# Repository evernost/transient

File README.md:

# transient
An analog synthesizer.

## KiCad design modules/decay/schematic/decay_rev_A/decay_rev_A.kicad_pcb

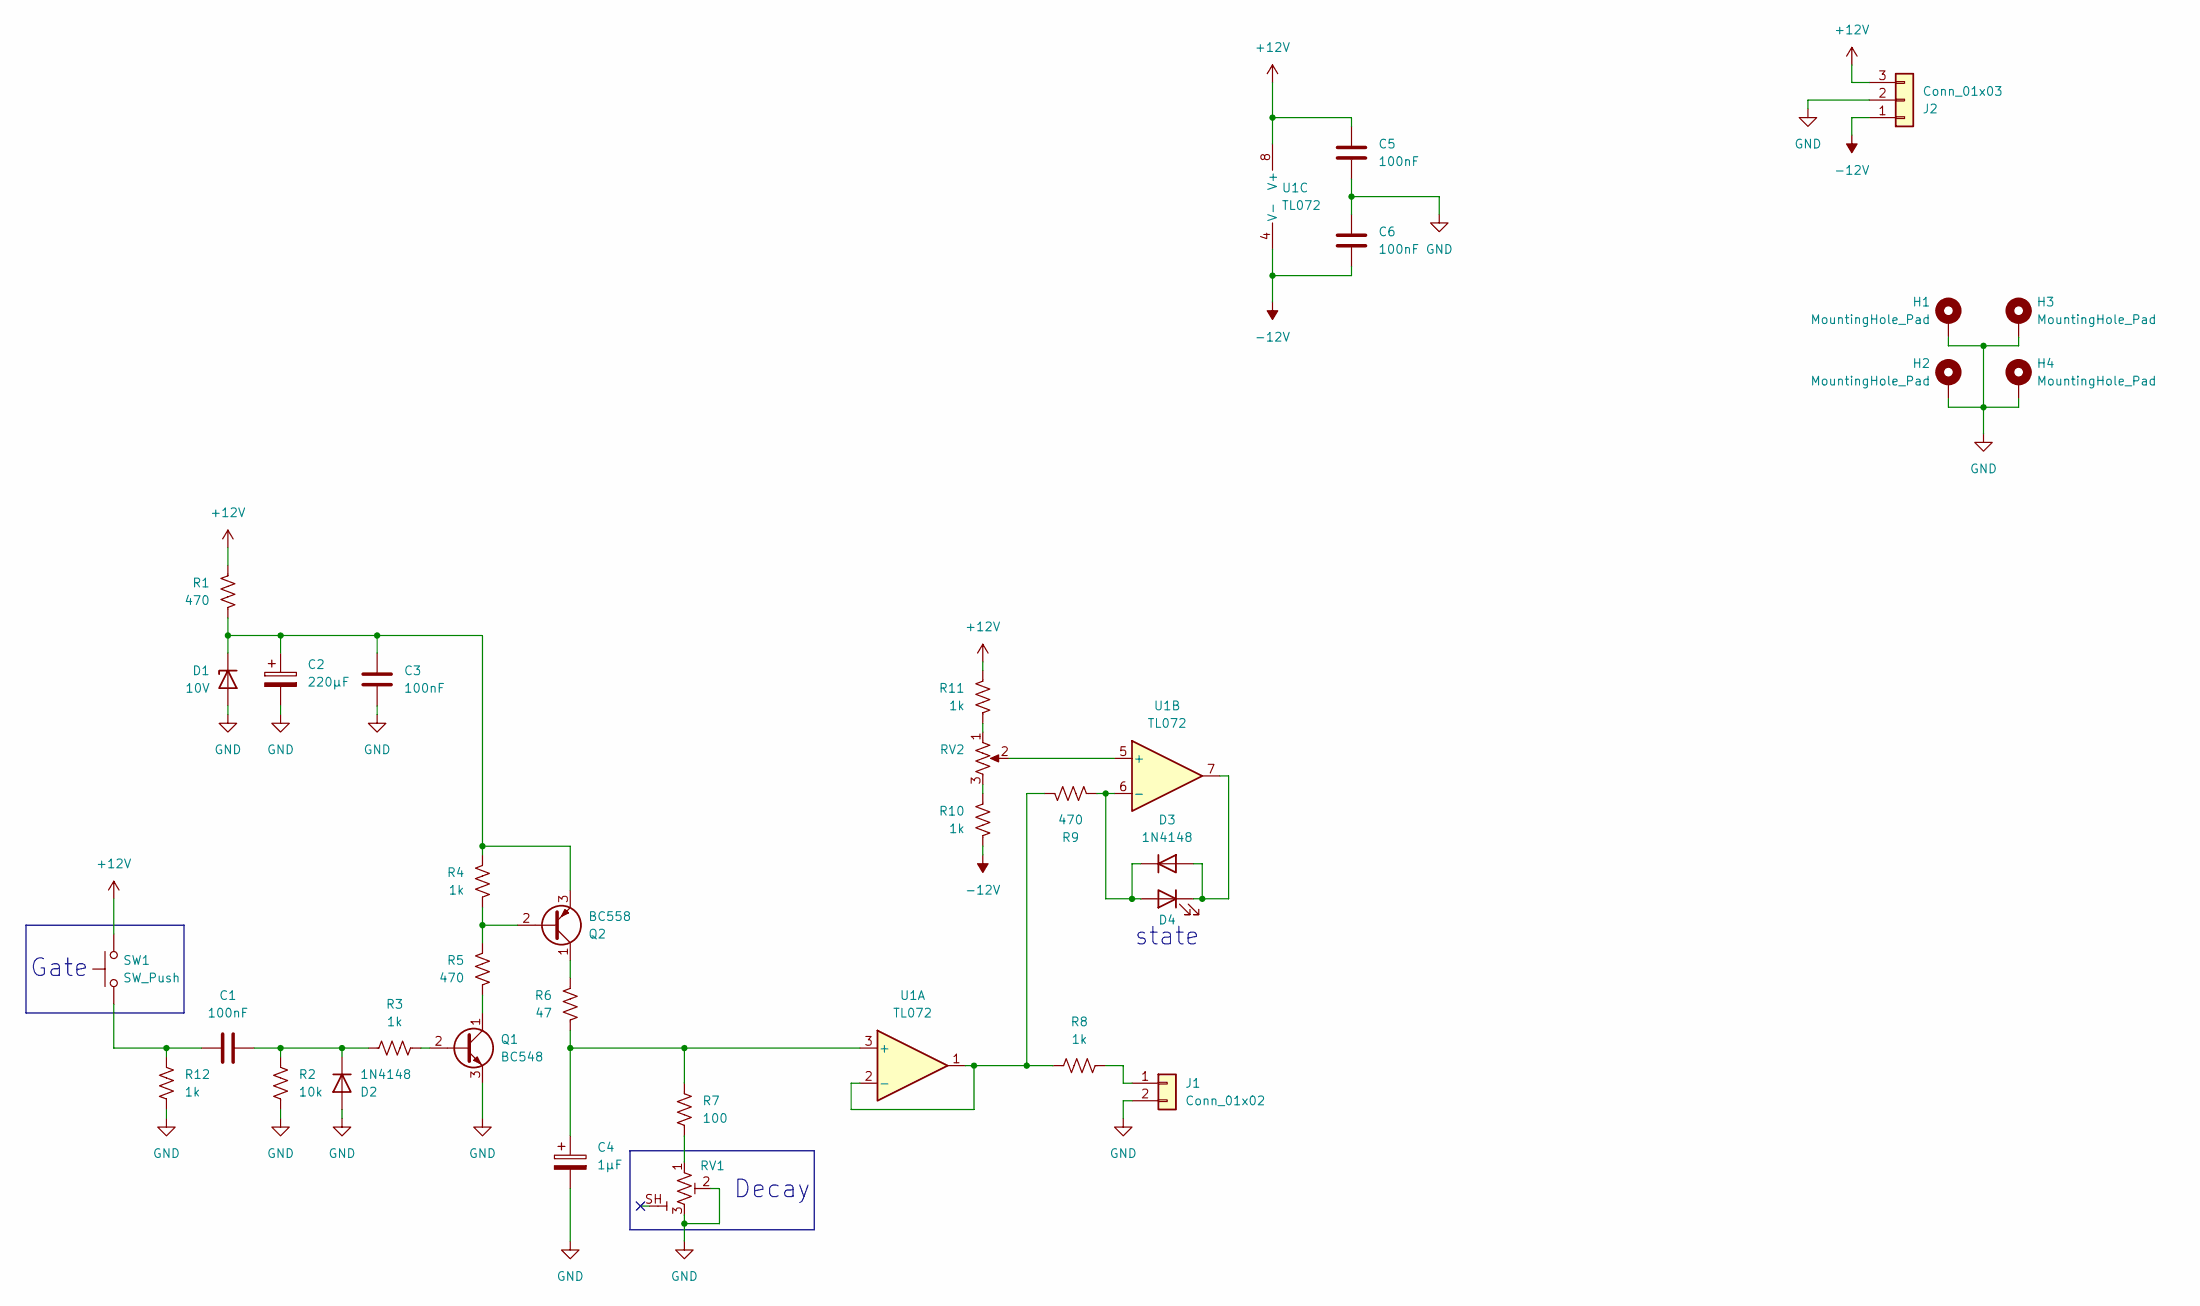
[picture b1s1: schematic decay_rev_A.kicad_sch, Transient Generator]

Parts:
C1, C3, C5, C6: 100nF; C_Rect_L7.0mm_W2.0mm_P5.00mm
C2: 220µF; CP_Radial_D10.0mm_P5.00mm
C4: 1µF; CP_Radial_D10.0mm_P5.00mm
D1: 10V; D_DO-35_SOD27_P10.16mm_Horizontal
D2, D3: 1N4148; D_DO-35_SOD27_P10.16mm_Horizontal
D4: LED; LED_D3.0mm
H1, H2, H3, H4: MountingHole_Pad; MountingHole_3.2mm_M3_Pad_Via
J1: Conn_01x02; PinHeader_1x02_P2.54mm_Vertical
J2: Conn_01x03; WuerthElectronik_WR_TBL_Series_2545_1x03_P5.08mm_Horizontal
Q1: BC548; TO-92L_Inline_Wide
Q2: BC558; TO-92L_Inline_Wide
R1, R5, R9: 470; R_Axial_DIN0207_L6.3mm_D2.5mm_P10.16mm_Horizontal
R2: 10k; R_Axial_DIN0207_L6.3mm_D2.5mm_P10.16mm_Horizontal
R3, R4, R8, R10, R11, R12: 1k; R_Axial_DIN0207_L6.3mm_D2.5mm_P10.16mm_Horizontal
R6: 47; R_Axial_DIN0207_L6.3mm_D2.5mm_P10.16mm_Horizontal
R7: 100; R_Axial_DIN0207_L6.3mm_D2.5mm_P10.16mm_Horizontal
RV1: R_Potentiometer_Shield_US; Potentiometer_Bourns_PTV09A-4_Single_Vertical
RV2: R_Potentiometer_US; Potentiometer_Bourns_3296W_Vertical
SW1: SW_Push; SW_Push_1P1T_NO_CK_KSC6xxG
U1: TL072; DIP-8_W7.62mm_LongPads

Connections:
+12V: C5.1, J2.3, R1.1, R11.2, SW1.2, U1.8 (V+)
-12V: C6.1, J2.1, R10.1, U1.4 (V-)
GND: C2.2, C3.2, C4.2, C5.2, C6.2, D1.2 (A), D2.2 (A), H1.1 (1_1), H2.1 (1_1), H3.1 (1_1), H4.1 (1_1), J1.2, J2.2, Q1.3 (E), R2.2, R12.2, RV1.2 (W), RV1.3 (B)
unnamed: C1.1, R12.1, SW1.1
unnamed: C2.1, C3.1, D1.1 (K), Q2.3 (E), R1.2, R4.1
unnamed: C1.2, D2.1 (K), R2.1, R3.1
unnamed: D3.2 (A), D4.1 (K), U1.7
unnamed: D3.1 (K), D4.2 (A), R9.1, U1.6 (-)
unnamed: J1.1, R8.2
unnamed: Q1.2 (B), R3.2
unnamed: Q1.1 (C), R5.2
unnamed: Q2.2 (B), R4.2, R5.1
unnamed: Q2.1 (C), R6.1
unnamed: R10.2, RV2.3
unnamed: R11.1, RV2.1
unnamed: R7.2, RV1.1 (A)
unnamed: C4.1, R6.2, R7.1, U1.3 (+)
unnamed: R8.1, R9.2, U1.1, U1.2 (-)
unnamed: RV2.2, U1.5 (+)

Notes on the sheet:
Decay
Gate
state

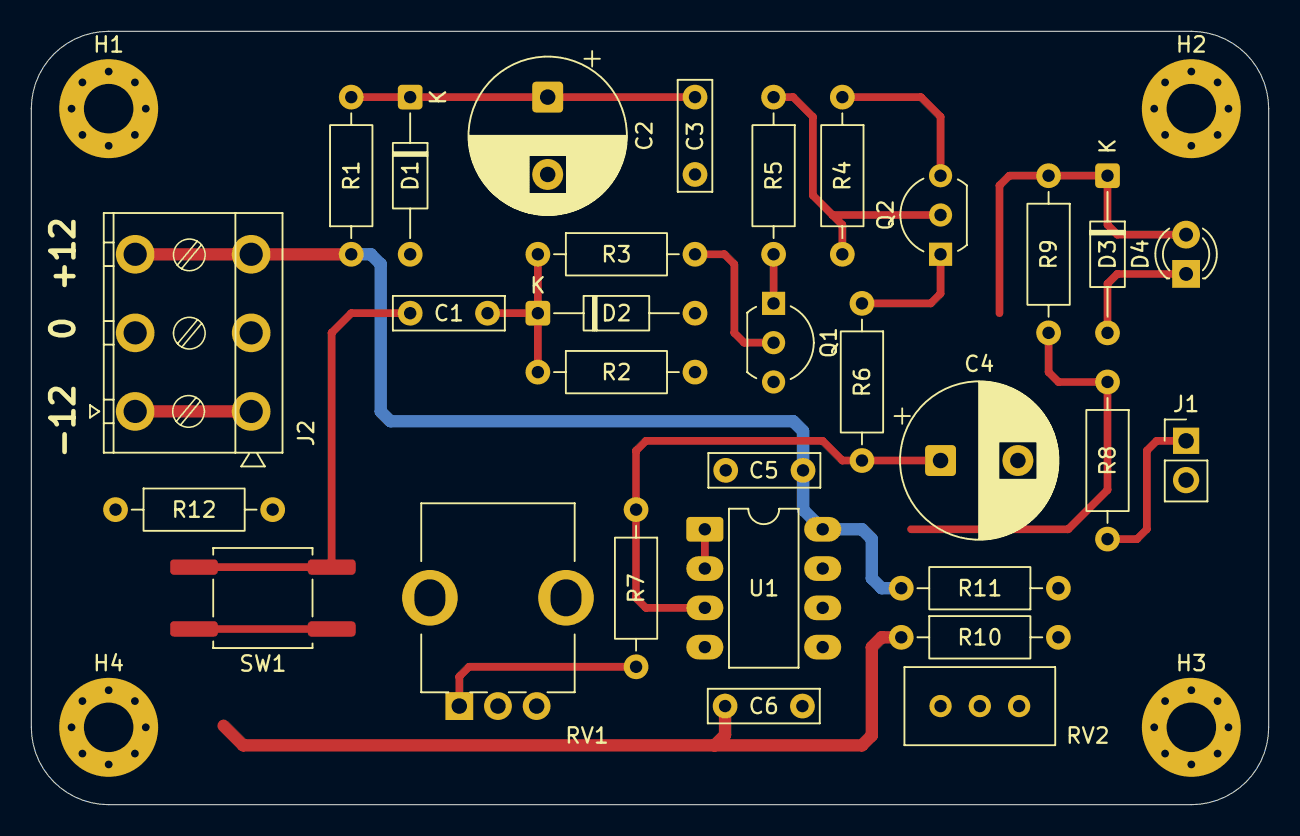
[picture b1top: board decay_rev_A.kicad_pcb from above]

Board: 2 copper layers, 80.0 x 50.0 mm, 34 parts (0 on the bottom side), 19 nets.

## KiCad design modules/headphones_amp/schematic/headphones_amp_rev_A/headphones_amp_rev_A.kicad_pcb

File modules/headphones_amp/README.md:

# Headphones Amplifier

Output stage module for headphones with gain and balance control.

---

## Overview

- **Type:** Amplifier
- **Domain:** Analog
- **Status:** Work in progress

Block diagram: TODO!

---

## Features
- Stereo amplifier
- Balance knob
- Volume knob
- Single power supply (+12V)
- Input impedance: TBD Ohms
- Output impedance: 32 Ohms
- Overload indicator (excessive power)

---

## Interfaces

### Inputs
| Name | Type | Range | Description |
|-----|------|-------|-------------|
| IN | Audio | ±1V | Input signal |
| AMP_CV | Analog | 0–5 V | Volume control |

### Outputs
| Name | Type | Description |
|------|------|-------------|
| OUT | Audio | Filtered signal |

---

## Controls

| Control | Type | Description |
|--------|------|-------------|
| Cutoff | Potentiometer | Manual cutoff frequency |
| Resonance | Potentiometer | Feedback amount |

---

## Electrical Characteristics

- **Supply voltage:** +12V
- **Current consumption:** TBD mA
- **Signal levels:** TBD

---

## Implementation Notes
Section is TODO.

---

## Files

| File                              | Description                           |
|-----------------------------------|---------------------------------------|
| `headphones_amp_rev_A.pdf`        | Electrical schematic (PDF export)     |
| `headphones_amp_rev_A.kicad_sch`  | Schematic (KiCad 10.0.8)              |
| `headphones_amp_rev_A.kicad_pcb`  | PCB layout (KiCad 10.0.8)             |
| `sim/XXX.asc`                     | SPICE simulation of the final stage   |

---

## Tools
Designed with KiCAD 10.0.8

### KiCAD Grid Settings

| Name   | Size    | Description        |
|--------|---------|--------------------|
| Grid 1 | 0.25 mm | PCB outline        |
| Grid 2 | 25 mil  | Parts placement    |
| Grid 3 | 25 mil  | Routing            |

**Rationale**: Grid 2 and Grid 3 were initially 50 mil, but turned out to be too coarse for precise tracks.

### KiCAD Track settings

| Name    | Size   | Description                |
|---------|--------|----------------------------|
| Class 1 | 500 um | Regular traces (signal)    |
| Class 2 | 800 um | Power traces               |

---

## Calibration / Tuning
- Tune the bias voltage on $Q_5$ and $Q_{11}$
- Tune the quiescent current 
- Tune the overload threshold

---

## Known Issues / TODO

- [ ] Make the bias point higher: 1.6V might clip too early
- [ ] Add a reverse polarity protection

---

## Revision History

| Revision | Date | Notes |
|--------|------|-------|
| Rev A | YYYY-MM-DD | Initial prototype |
| Rev B | YYYY-MM-DD | Fixed grounding issue |

---

## Related Modules

Links to other submodules in the repository:
- `../vca/`
- `../ring_modulator/`

---

## References
- Elektor Voiced/Devoiced detector, April 1981 p.32-33

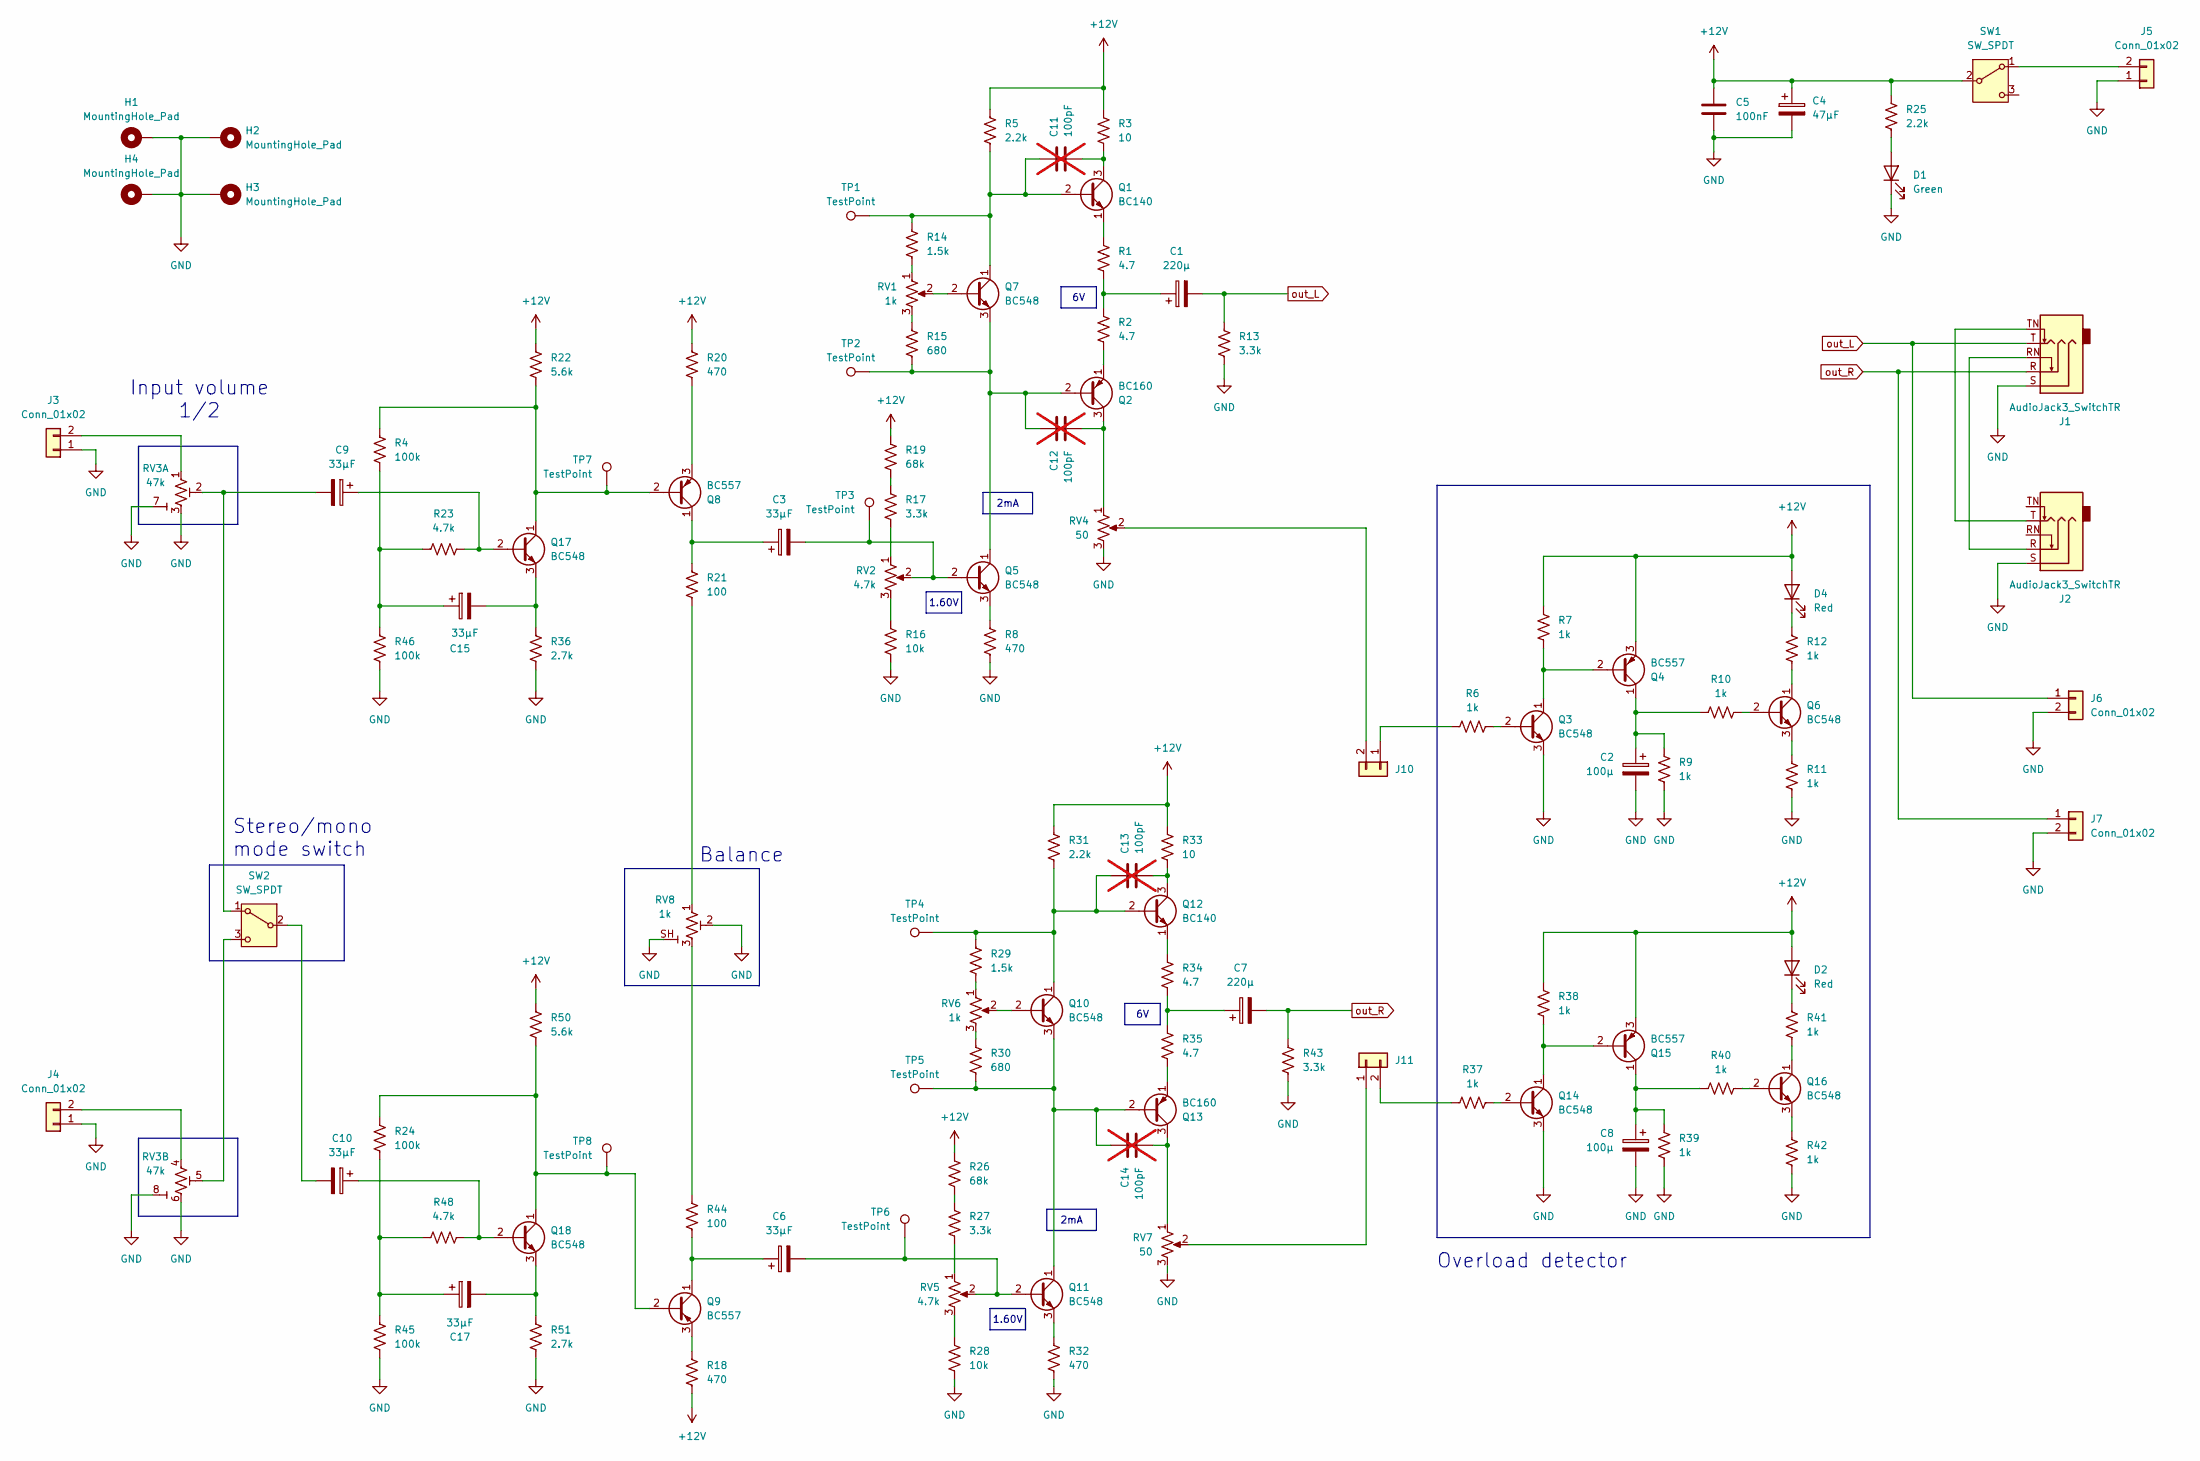
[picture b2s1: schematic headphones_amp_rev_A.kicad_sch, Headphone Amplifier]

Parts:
C1, C7: 220µ; CP_Radial_D10.0mm_P5.00mm
C2, C8: 100µ; CP_Radial_D10.0mm_P5.00mm
C3, C6, C9, C10, C15, C17: 33µF; CP_Radial_D10.0mm_P5.00mm
C4: 47µF; CP_Radial_D10.0mm_P5.00mm
C5: 100nF; C_Rect_L7.0mm_W2.0mm_P5.00mm
C11, C12, C13, C14: 100pF; C_Rect_L7.0mm_W2.0mm_P5.00mm; not fitted
D1: Green; LED_D3.0mm
D2, D4: Red; LED_D3.0mm
H1, H2, H3, H4: MountingHole_Pad; MountingHole_3.2mm_M3_Pad_Via
J1: AudioJack3_SwitchTR; Jack_6.35mm_Neutrik_NRJ6HM-1-PRE_Horizontal
J2: AudioJack3_SwitchTR; Jack_3.5mm_CUI_SJ1-3515N_Horizontal
J3, J4, J6, J7: Conn_01x02; WuerthElectronik_WR_TBL_Series_2109_1x02_P2.54mm_Horizontal
J5: Conn_01x02; WuerthElectronik_WR_TBL_Series_2545_1x02_P5.08mm_Horizontal
J10, J11: Conn_01x02; PinHeader_1x02_P2.54mm_Vertical
Q1, Q12: BC140; TO-39-3
Q2, Q13: BC160; TO-39-3
Q3, Q5, Q6, Q7, Q10, Q11, Q14, Q16, Q17, Q18: BC548; TO-92L_Inline_Wide
Q4, Q8, Q9, Q15: BC557; TO-92L_Inline_Wide
R1, R2, R34, R35: 4.7; R_Axial_DIN0207_L6.3mm_D2.5mm_P10.16mm_Horizontal
R3, R33: 10; R_Axial_DIN0207_L6.3mm_D2.5mm_P10.16mm_Horizontal
R4, R24, R45, R46: 100k; R_Axial_DIN0207_L6.3mm_D2.5mm_P10.16mm_Horizontal
R5, R25, R31: 2.2k; R_Axial_DIN0207_L6.3mm_D2.5mm_P10.16mm_Horizontal
R6, R7, R9, R10, R11, R12, R37, R38, R39, R40, R41, R42: 1k; R_Axial_DIN0207_L6.3mm_D2.5mm_P10.16mm_Horizontal
R8, R18, R20, R32: 470; R_Axial_DIN0207_L6.3mm_D2.5mm_P10.16mm_Horizontal
R13, R17, R27, R43: 3.3k; R_Axial_DIN0207_L6.3mm_D2.5mm_P10.16mm_Horizontal
R14, R29: 1.5k; R_Axial_DIN0207_L6.3mm_D2.5mm_P10.16mm_Horizontal
R15, R30: 680; R_Axial_DIN0207_L6.3mm_D2.5mm_P10.16mm_Horizontal
R16, R28: 10k; R_Axial_DIN0207_L6.3mm_D2.5mm_P10.16mm_Horizontal
R19, R26: 68k; R_Axial_DIN0207_L6.3mm_D2.5mm_P10.16mm_Horizontal
R21, R44: 100; R_Axial_DIN0207_L6.3mm_D2.5mm_P10.16mm_Horizontal
R22, R50: 5.6k; R_Axial_DIN0207_L6.3mm_D2.5mm_P10.16mm_Horizontal
R23, R48: 4.7k; R_Axial_DIN0207_L6.3mm_D2.5mm_P10.16mm_Horizontal
R36, R51: 2.7k; R_Axial_DIN0207_L6.3mm_D2.5mm_P10.16mm_Horizontal
RV1, RV6: 1k; Potentiometer_Bourns_3296W_Vertical
RV2, RV5: 4.7k; Potentiometer_Bourns_3296W_Vertical
RV3: 47k; Potentiometer_Bourns_PTV112-4_Dual_Vertical
RV4, RV7: 50; Potentiometer_Bourns_3296W_Vertical
RV8: 1k; Potentiometer_Bourns_PTV09A-4_Single_Vertical
SW1, SW2: SW_SPDT; SW_CIT_ANT13_SPDT_Straight
TP1, TP2, TP3, TP4, TP5, TP6, TP7, TP8: TestPoint; TestPoint_Pad_D2.0mm

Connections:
+12V: C4.1, C5.1, D2.2 (A), D4.2 (A), Q4.3 (E), Q15.3 (E), R3.1, R5.1, R7.1, R18.2, R19.2, R20.1, R22.1, R25.1, R26.2, R31.1, R33.1, R38.1, R50.1, SW1.2
GND: C2.2, C4.2, C5.2, C8.2, D1.1 (K), H1.1 (1_1), H2.1 (1_1), H3.1 (1_1), H4.1 (1_1), J1.S, J2.S, J3.1, J4.1, J5.1, J6.2, J7.2, Q3.3 (E), Q14.3 (E), R8.2, R9.2, R11.2, R13.2, R16.2, R28.2, R32.2, R36.2, R39.2, R42.2, R43.2, R45.2, R46.2, R51.2, RV3.3 (B), RV3.6 (B), RV3.7 (SH1), RV3.8 (SH2), RV4.3, RV7.3, RV8.2 (W), RV8.SH
unnamed: C1.1, R1.2, R2.1
unnamed: C7.1, R34.2, R35.1
unnamed: C10.2, SW2.2
unnamed: C15.1, R4.2, R23.1, R46.1
unnamed: C17.1, R24.2, R45.1, R48.1
unnamed: D1.2 (A), R25.2
unnamed: D2.1 (K), R41.1
unnamed: D4.1 (K), R12.1
unnamed: J1.RN, J2.R
unnamed: J1.TN, J2.T
unnamed: J3.2, RV3.1 (A)
unnamed: J4.2, RV3.4 (A)
unnamed: J5.2, SW1.1
unnamed: J10.1, R6.1
unnamed: J10.2, RV4.2
unnamed: J11.1, RV7.2
unnamed: J11.2, R37.1
unnamed: C11.1, Q1.2 (B), Q7.1 (C), R5.2, R14.1, TP1.1 (1_1)
unnamed: C11.2, Q1.3 (C), R3.2
unnamed: Q1.1 (E), R1.1
unnamed: C12.1, Q2.2 (B), Q5.1 (C), Q7.3 (E), R15.2, TP2.1 (1_1)
unnamed: C12.2, Q2.3 (C), RV4.1
unnamed: Q2.1 (E), R2.2
unnamed: Q3.2 (B), R6.2
unnamed: Q3.1 (C), Q4.2 (B), R7.2
unnamed: C2.1, Q4.1 (C), R9.1, R10.1
unnamed: C3.2, Q5.2 (B), RV2.2, TP3.1 (1_1)
unnamed: Q5.3 (E), R8.1
unnamed: Q6.2 (B), R10.2
unnamed: Q6.1 (C), R12.2
unnamed: Q6.3 (E), R11.1
unnamed: Q7.2 (B), RV1.2
unnamed: C3.1, Q8.1 (C), R21.1
unnamed: Q8.3 (E), R20.2
unnamed: C6.1, Q9.1 (C), R44.2
unnamed: Q9.3 (E), R18.1
unnamed: Q10.2 (B), RV6.2
unnamed: C13.1, Q10.1 (C), Q12.2 (B), R29.1, R31.2, TP4.1 (1_1)
unnamed: C14.1, Q10.3 (E), Q11.1 (C), Q13.2 (B), R30.2, TP5.1 (1_1)
unnamed: C6.2, Q11.2 (B), RV5.2, TP6.1 (1_1)
unnamed: Q11.3 (E), R32.1
unnamed: C13.2, Q12.3 (C), R33.2
unnamed: Q12.1 (E), R34.1
unnamed: C14.2, Q13.3 (C), RV7.1
unnamed: Q13.1 (E), R35.2
unnamed: Q14.2 (B), R37.2
unnamed: Q14.1 (C), Q15.2 (B), R38.2
unnamed: C8.1, Q15.1 (C), R39.1, R40.1
unnamed: Q16.2 (B), R40.2
unnamed: Q16.1 (C), R41.2
unnamed: Q16.3 (E), R42.1
unnamed: C9.1, Q17.2 (B), R23.2
unnamed: Q8.2 (B), Q17.1 (C), R4.1, R22.2, TP7.1 (1_1)
unnamed: C15.2, Q17.3 (E), R36.1
unnamed: C10.1, Q18.2 (B), R48.2
unnamed: Q9.2 (B), Q18.1 (C), R24.1, R50.2, TP8.1 (1_1)
unnamed: C17.2, Q18.3 (E), R51.1
unnamed: R14.2, RV1.1
unnamed: R15.1, RV1.3
unnamed: R16.1, RV2.3
unnamed: R17.1, R19.1
unnamed: R17.2, RV2.1
unnamed: R26.1, R27.1
unnamed: R27.2, RV5.1
unnamed: R28.1, RV5.3
unnamed: R29.2, RV6.1
unnamed: R30.1, RV6.3
unnamed: C9.2, RV3.2 (W), SW2.1
unnamed: RV3.5 (W), SW2.3
unnamed: R21.2, RV8.1 (A)
unnamed: R44.1, RV8.3 (B)
out_L: C1.2, J1.T, J6.1, R13.1
out_R: C7.2, J1.R, J7.1, R43.1

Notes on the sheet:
Stereo/mono mode switch
Overload detector
Input volume 1/2
Balance
1.60V
2mA

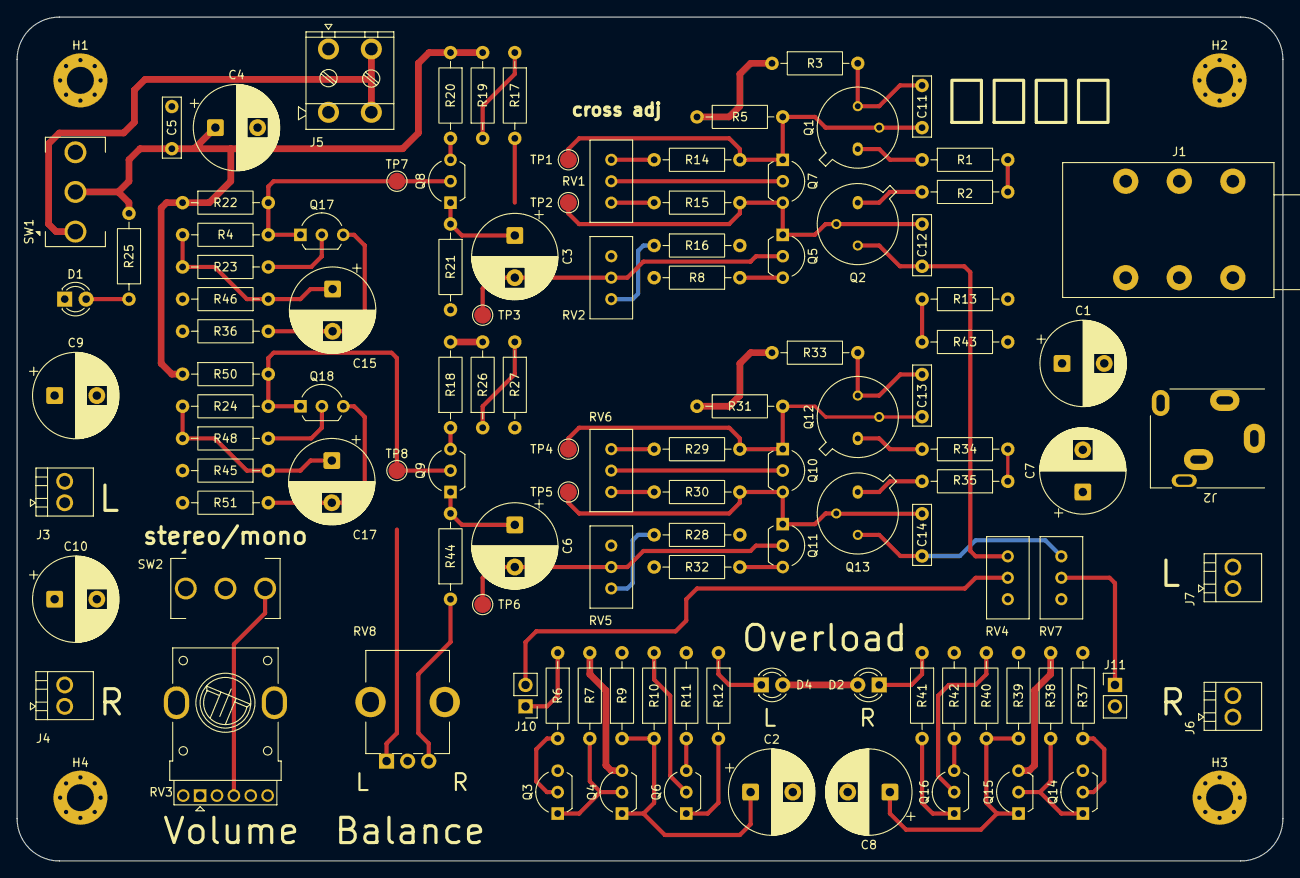
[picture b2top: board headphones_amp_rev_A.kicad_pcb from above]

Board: 2 copper layers, 150.0 x 100.0 mm, 117 parts (0 on the bottom side), 75 nets.

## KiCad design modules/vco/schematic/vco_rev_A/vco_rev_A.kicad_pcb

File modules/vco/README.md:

# VCO Module

Voltage-Controlled Module, with digital control for accurate tuning.

<!-- Example:
> This module implements a voltage-controlled low-pass filter based on a 4-pole ladder topology, intended for use in the analog signal path. -->

---

## Overview

- **Type:** VCO
- **Domain:** Analog, with Digital stabilisation
- **Status:** Work in progress

Block diagram: TODO!

---

## Features

- **Waveforms**: Sawtooth, Rectangular
- **Control**: exponential (1V/oct)
- **Inner Modulation**: up to 2 synchronised modulators to add more depth 
- **Sync**: digital input for synchronisation effect + random synchronisation

---

## Interfaces

### Inputs
| Name | Type | Range | Description |
|-----|------|-------|-------------|
| TODO | TODO | TODO |

### Outputs
| Name | Type | Description |
|------|------|-------------|
| TODO | TODO | TODO |

---

## Controls

| Control | Type | Description |
|--------|------|-------------|
| TODO | TODO | TODO |

---

## Electrical Characteristics

- **Supply voltage:** ±12V
- **Current consumption:** TBD mA
- **Signal levels:** TBD

---

## Implementation Notes

Design details, assumptions, or decisions worth remembering later.

Examples:
- Filter core based on [reference / paper / IC]
- Uses matched transistor pair for temperature stability
- Digital control smoothed with RC + oversampling

---

## Files

| File                  | Description                       |
|-----------------------|-----------------------------------|
| `vco_rev_A.pdf`       | Electrical schematic (PDF export) |
| `vco_rev_A.kicad_sch` | Schematic (KiCad 10.0.8)          |
| `vco_rev_A.kicad_pcb` | PCB layout (KiCad 10.0.8)|
| `firmware/`           | Embedded code for the VCO (STM32CubeIDE 2.1.1 - 2026) |

---

## Calibration / Tuning
> This section is TODO!

---

## Known Issues / TODO
- [ ] Create footprint for the STM32G441KB

---

## Revision History

| Revision | Date             | Notes                           |
|----------|------------------|---------------------------------|
| Rev A    | 10 November 2026 | Initial prototype               |
| Rev B    | TBA              | Added MCU for the tune control  |

---

## Related Modules

Links to other submodules in the repository:
- `../vca/`
- `../ring_modulator/`

---

## References
- Elektor FORMANT, Chapter 4 and 5

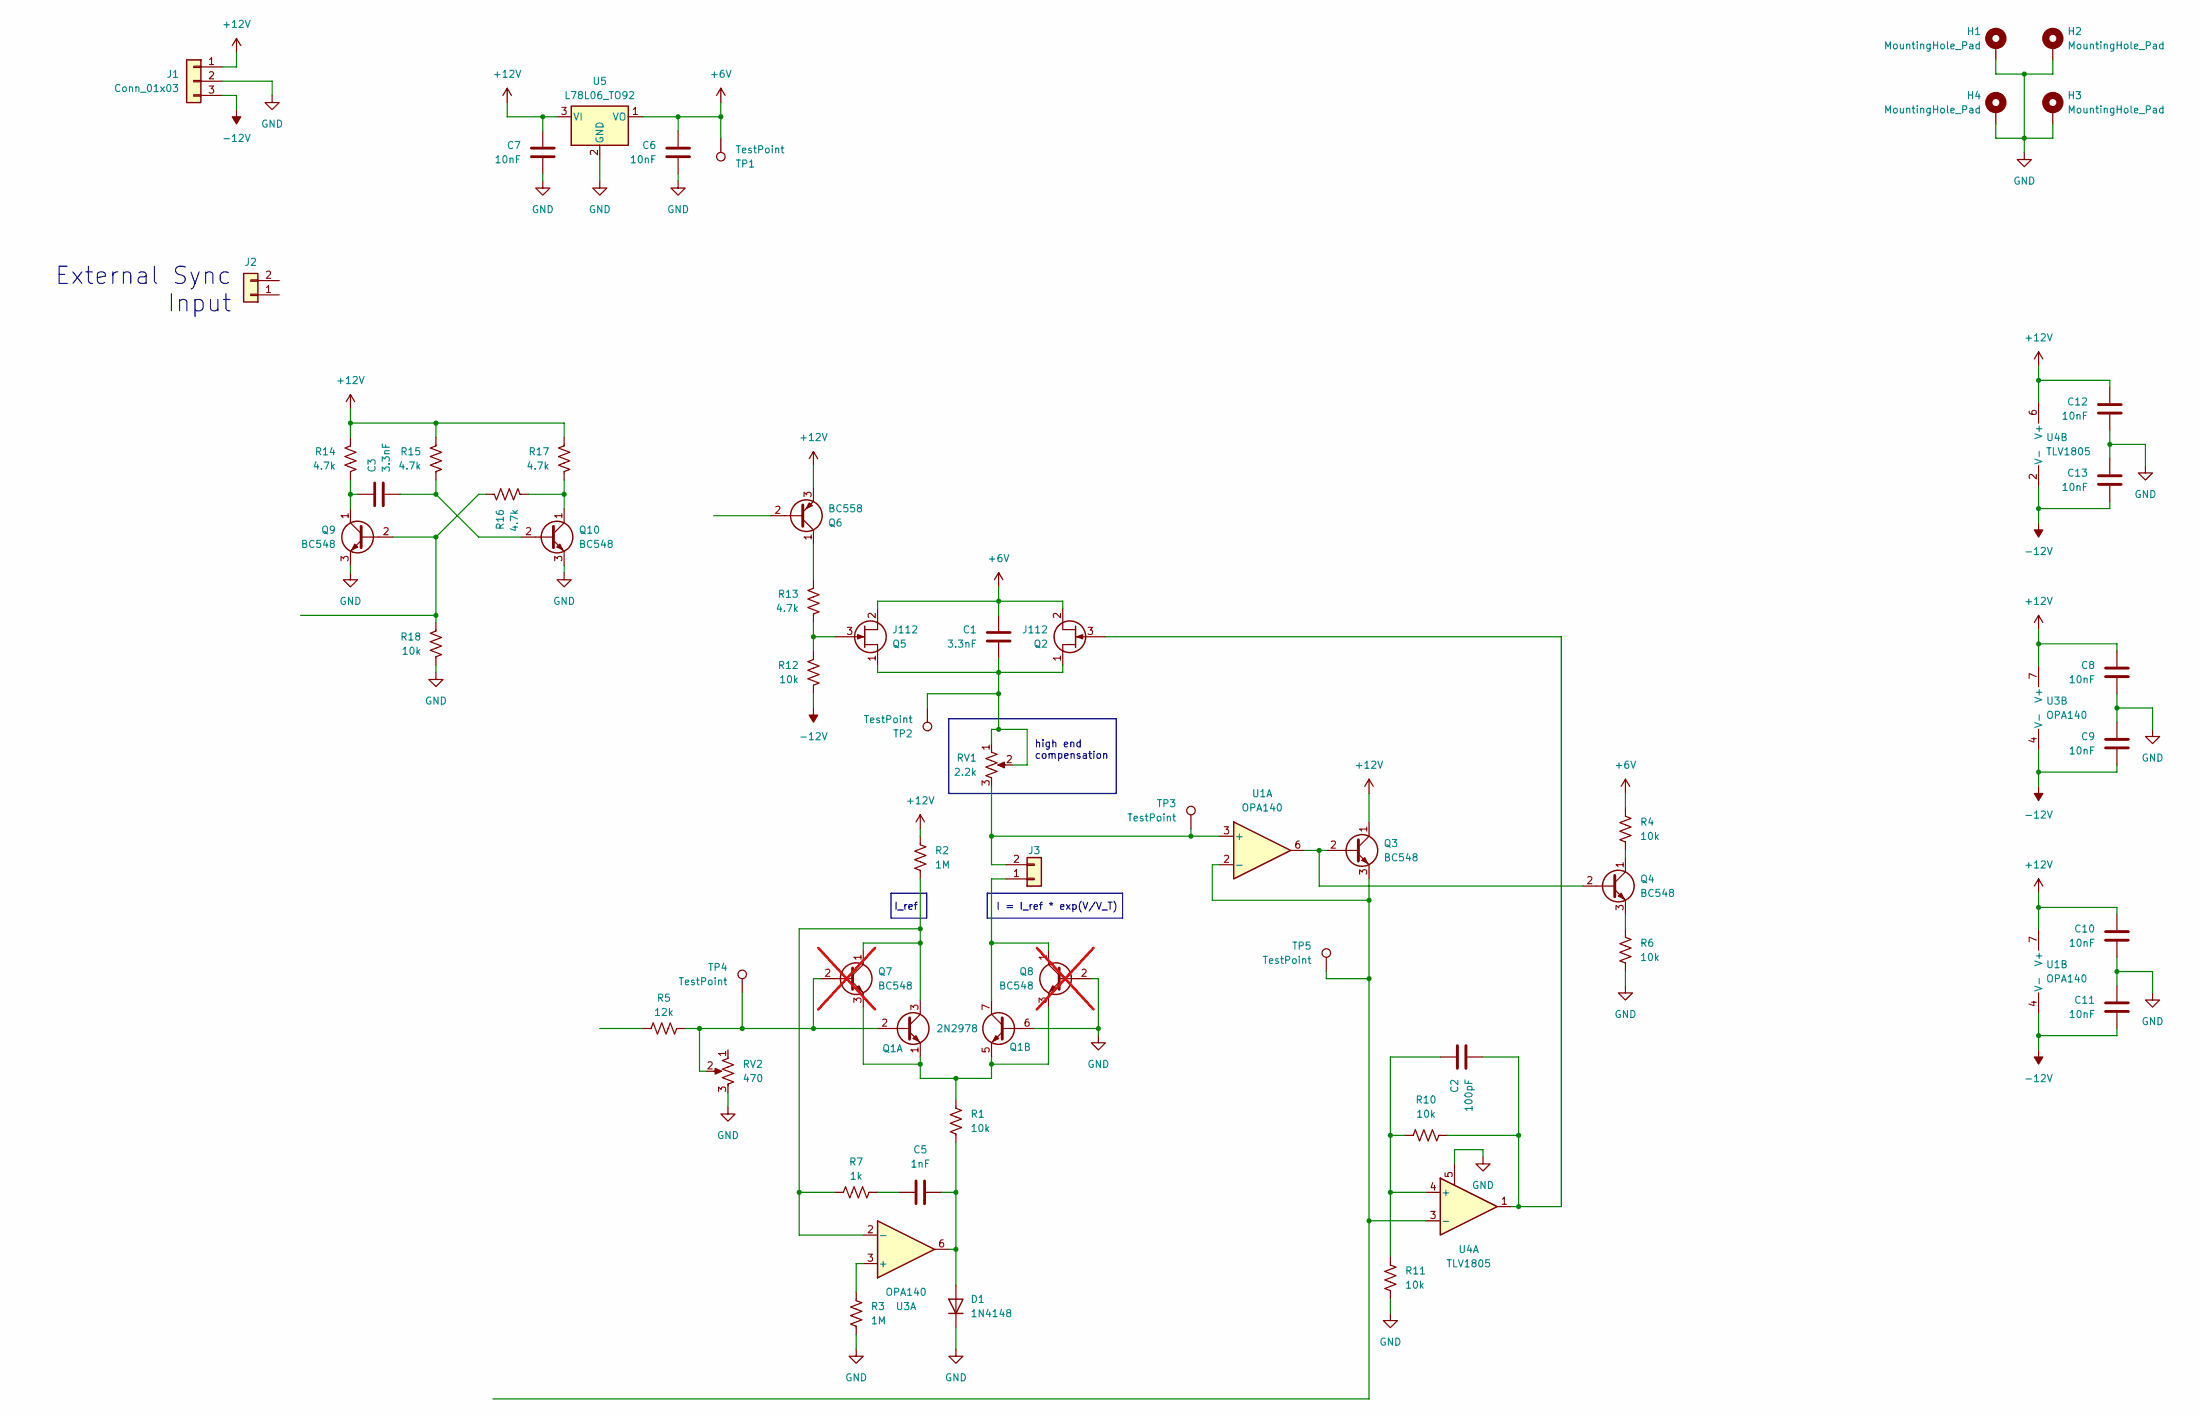
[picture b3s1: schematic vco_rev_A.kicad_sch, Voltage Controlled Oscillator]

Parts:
C1, C3: 3.3nF; C_Rect_L7.0mm_W2.0mm_P5.00mm
C2: 100pF; C_Rect_L7.0mm_W2.0mm_P5.00mm
C5: 1nF; C_0805_2012Metric_Pad1.18x1.45mm_HandSolder
C6, C7, C8, C9, C10, C11, C12, C13: 10nF; C_Rect_L7.0mm_W2.0mm_P5.00mm
D1: 1N4148; D_DO-35_SOD27_P10.16mm_Horizontal
H1, H2, H3, H4: MountingHole_Pad; MountingHole_3.2mm_M3_Pad_Via
J1: Conn_01x03; WuerthElectronik_WR_TBL_Series_2545_1x03_P5.08mm_Horizontal
J2, J3: Conn_01x02; PinHeader_1x02_P2.54mm_Vertical
Q1: 2N2978; TO-5-6
Q2, Q5: J112; TO-92_Inline_Wide
Q3, Q4, Q9, Q10: BC548; TO-92L_Inline_Wide
Q6: BC558; TO-92L_Inline_Wide
Q7, Q8: BC548; TO-92L_Inline_Wide; not fitted
R1, R4, R6, R10, R11, R12, R18: 10k; R_Axial_DIN0207_L6.3mm_D2.5mm_P10.16mm_Horizontal
R2, R3: 1M; R_Axial_DIN0207_L6.3mm_D2.5mm_P10.16mm_Horizontal
R5: 12k; R_Axial_DIN0207_L6.3mm_D2.5mm_P10.16mm_Horizontal
R7: 1k; R_Axial_DIN0207_L6.3mm_D2.5mm_P10.16mm_Horizontal
R13, R14, R15, R16, R17: 4.7k; R_Axial_DIN0207_L6.3mm_D2.5mm_P10.16mm_Horizontal
RV1: 2.2k; Potentiometer_Bourns_3296W_Vertical
RV2: 470; Potentiometer_Bourns_3296W_Vertical
TP1, TP2, TP3, TP4, TP5: TestPoint; TestPoint_Pad_D2.0mm
U1, U3: OPA140; VSSOP-8_3x3mm_P0.65mm
U4: TLV1805; SOT-23-6_Handsoldering
U5: L78L06_TO92; TO-92L_Inline_Wide

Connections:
+6V: C1.1, C6.1, Q2.2 (S), Q5.2 (S), R4.1, TP1.1 (1_1), U5.1 (VO)
+12V: C7.1, C8.1, C10.1, C12.1, J1.1, Q3.1 (C), Q6.3 (E), R2.1, R14.2, R15.2, R17.2, U1.7 (V+), U3.7 (V+), U4.6 (V+), U5.3 (VI)
-12V: C9.2, C11.2, C13.2, J1.3, R12.1, U1.4 (V-), U3.4 (V-), U4.2 (V-)
GND: C6.2, C7.2, C8.2, C9.1, C10.2, C11.1, C12.2, C13.1, D1.1 (K), H1.1 (1_1), H2.1 (1_1), H3.1 (1_1), H4.1 (1_1), J1.2, Q1.6 (B2), Q8.2 (B), Q9.3 (E), Q10.3 (E), R3.2, R6.2, R11.1, R18.1, RV2.3, U4.5, U5.2 (GND)
unnamed: C5.1, R7.2
unnamed: C5.2, D1.2 (A), R1.2, U3.6
unnamed: J3.1, Q1.7 (C2), Q8.1 (C)
unnamed: J3.2, RV1.3, TP3.1 (1_1), U1.3 (+)
unnamed: Q1.2 (B1), Q7.2 (B), R5.2, RV2.2, TP4.1 (1_1)
unnamed: Q1.3 (C1), Q7.1 (C), R2.2, R7.1, U3.2 (-)
unnamed: Q1.1 (E1), Q1.5 (E2), Q7.3 (E), Q8.3 (E), R1.1
unnamed: C1.2, Q2.1 (D), Q5.1 (D), RV1.1, RV1.2, TP2.1 (1_1)
unnamed: C2.2, Q2.3 (G), R10.2, U4.1
unnamed: Q3.2 (B), Q4.2 (B), U1.6
unnamed: Q3.3 (E), TP5.1 (1_1), U1.2 (-), U4.3 (-)
unnamed: Q4.1 (C), R4.2
unnamed: Q4.3 (E), R6.1
unnamed: Q5.3 (G), R12.2, R13.1
unnamed: Q6.1 (C), R13.2
unnamed: Q9.2 (B), R16.2, R18.2
unnamed: C3.1, Q9.1 (C), R14.1
unnamed: C3.2, Q10.2 (B), R15.1
unnamed: Q10.1 (C), R16.1, R17.1
unnamed: R3.1, U3.3 (+)
unnamed: C2.1, R10.1, R11.2, U4.4 (+)

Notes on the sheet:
I = I_ref * exp(V/V_T)
I_ref
high end compensation
External Sync Input

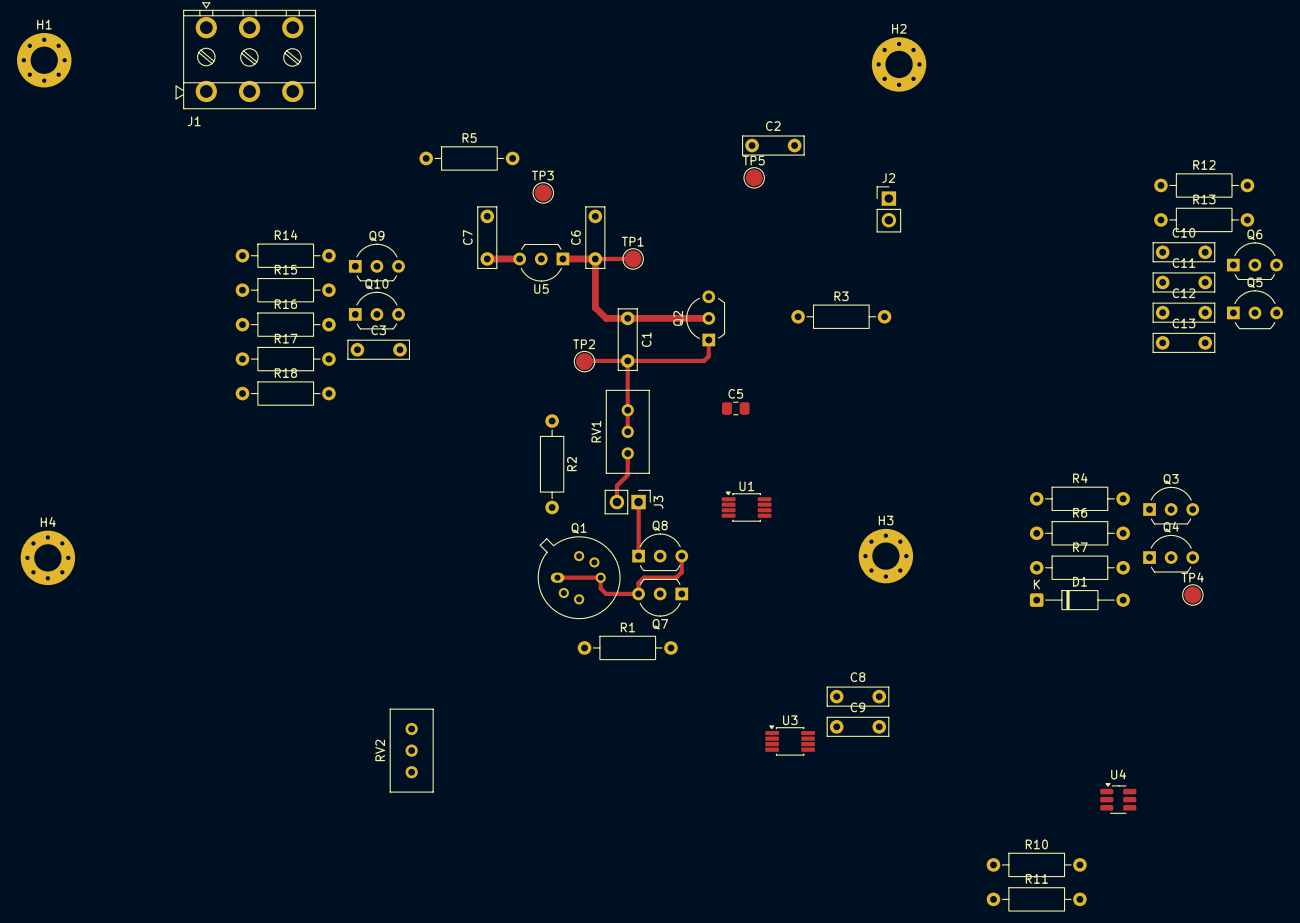
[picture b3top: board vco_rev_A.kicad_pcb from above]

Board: 2 copper layers, 57 parts (0 on the bottom side), 25 nets.
